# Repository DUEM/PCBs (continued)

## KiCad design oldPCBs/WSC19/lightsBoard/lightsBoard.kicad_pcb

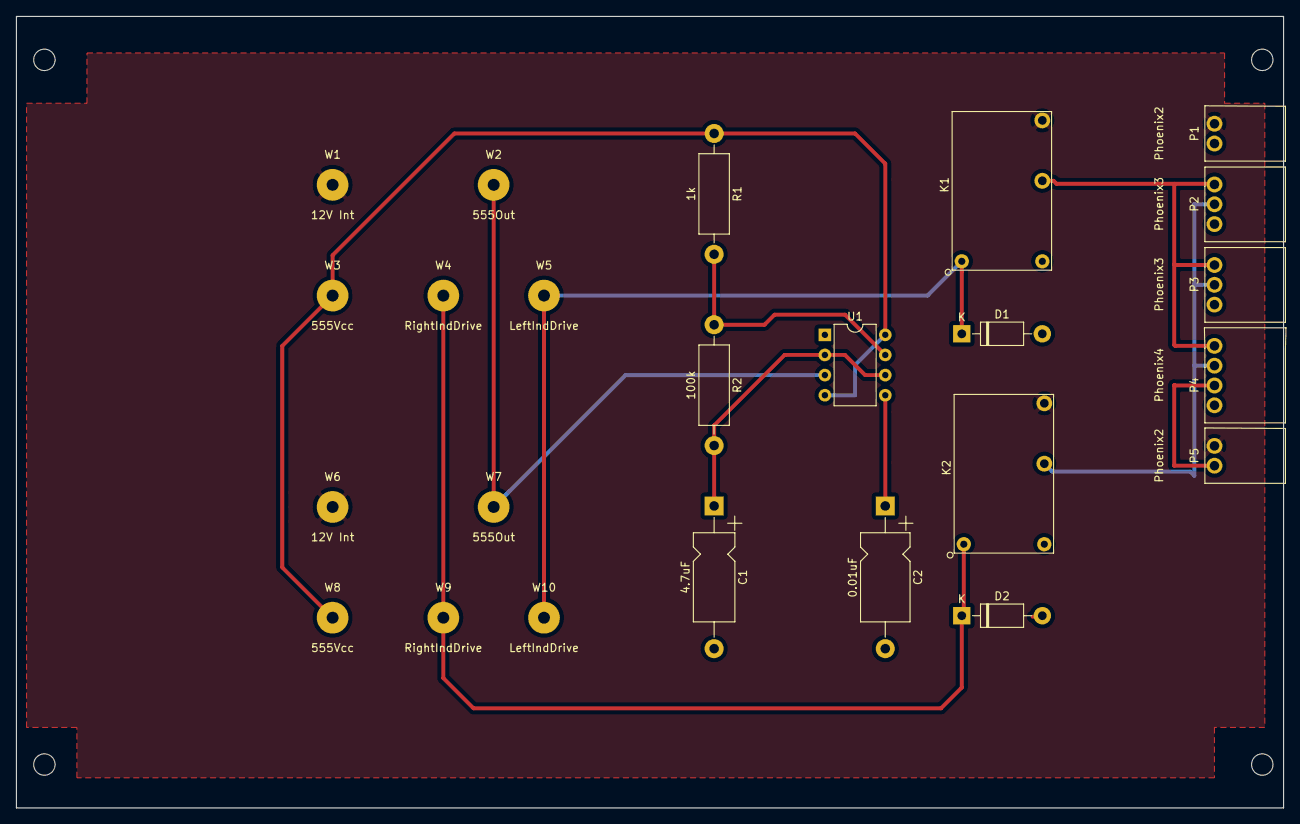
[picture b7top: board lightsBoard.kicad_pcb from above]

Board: 2 copper layers, 159.9 x 99.9 mm, 28 parts (0 on the bottom side), 12 nets.

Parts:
C1: 4.7uF; CP_Axial_L11.0mm_D5.0mm_P18.00mm_Horizontal
C2: 0.01uF; CP_Axial_L11.0mm_D6.0mm_P18.00mm_Horizontal
D1, D2: 1N4001; D_DO-41_SOD81_P10.16mm_Horizontal
K1, K2: DK; DKRelay
MK1, MK2, MK3, MK4: Mounting_Hole_PAD; MountingHole_2.7mm
P1, P5: Phoenix2; PhoenixSmol2
P2, P3: Phoenix3; PhoenixSmol3
P4: Phoenix4; PhoenixSmol4
R1: 1k; R_Axial_DIN0411_L9.9mm_D3.6mm_P15.24mm_Horizontal
R2: 100k; R_Axial_DIN0411_L9.9mm_D3.6mm_P15.24mm_Horizontal
U1: 555Timer; DIP-8_W7.62mm
W1, W6: 12V Int; SolderWirePad_1x01_Drill1.5mm
W2, W7: 555Out; SolderWirePad_1x01_Drill1.5mm
W3, W8: 555Vcc; SolderWirePad_1x01_Drill1.5mm
W4, W9: RightIndDrive; SolderWirePad_1x01_Drill1.5mm
W5, W10: LeftIndDrive; SolderWirePad_1x01_Drill1.5mm

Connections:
+12V: K1.4, K2.4, P1.1, P5.1, W1.1, W6.1
GND: C1.2, C2.2, D1.2, D2.2, K1.1, K2.1, P1.2, P2.3, P3.3, P4.4, U1.1
LeftDrive: D1.1, K1.6, W5.1, W10.1
unnamed: C1.1, R2.2, U1.2, U1.6
unnamed: C2.1, U1.5
unnamed: K1.3, P2.1, P3.1, P4.1
unnamed: K2.3, P2.2, P3.2, P4.2
unnamed: P4.3, P5.2
unnamed: R1.2, R2.1, U1.7
RightDrive: D2.1, K2.6, W4.1, W9.1
Vcc: R1.1, U1.4, U1.8, W3.1, W8.1
Vout: U1.3, W2.1, W7.1

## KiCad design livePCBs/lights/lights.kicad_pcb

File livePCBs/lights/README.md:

# Lights Board
- For iESC 2020
- The `const_current` components are separate daughterboards intended to supply a controllable constant current. These didn't work :( but the design files are on the DUSC drive.

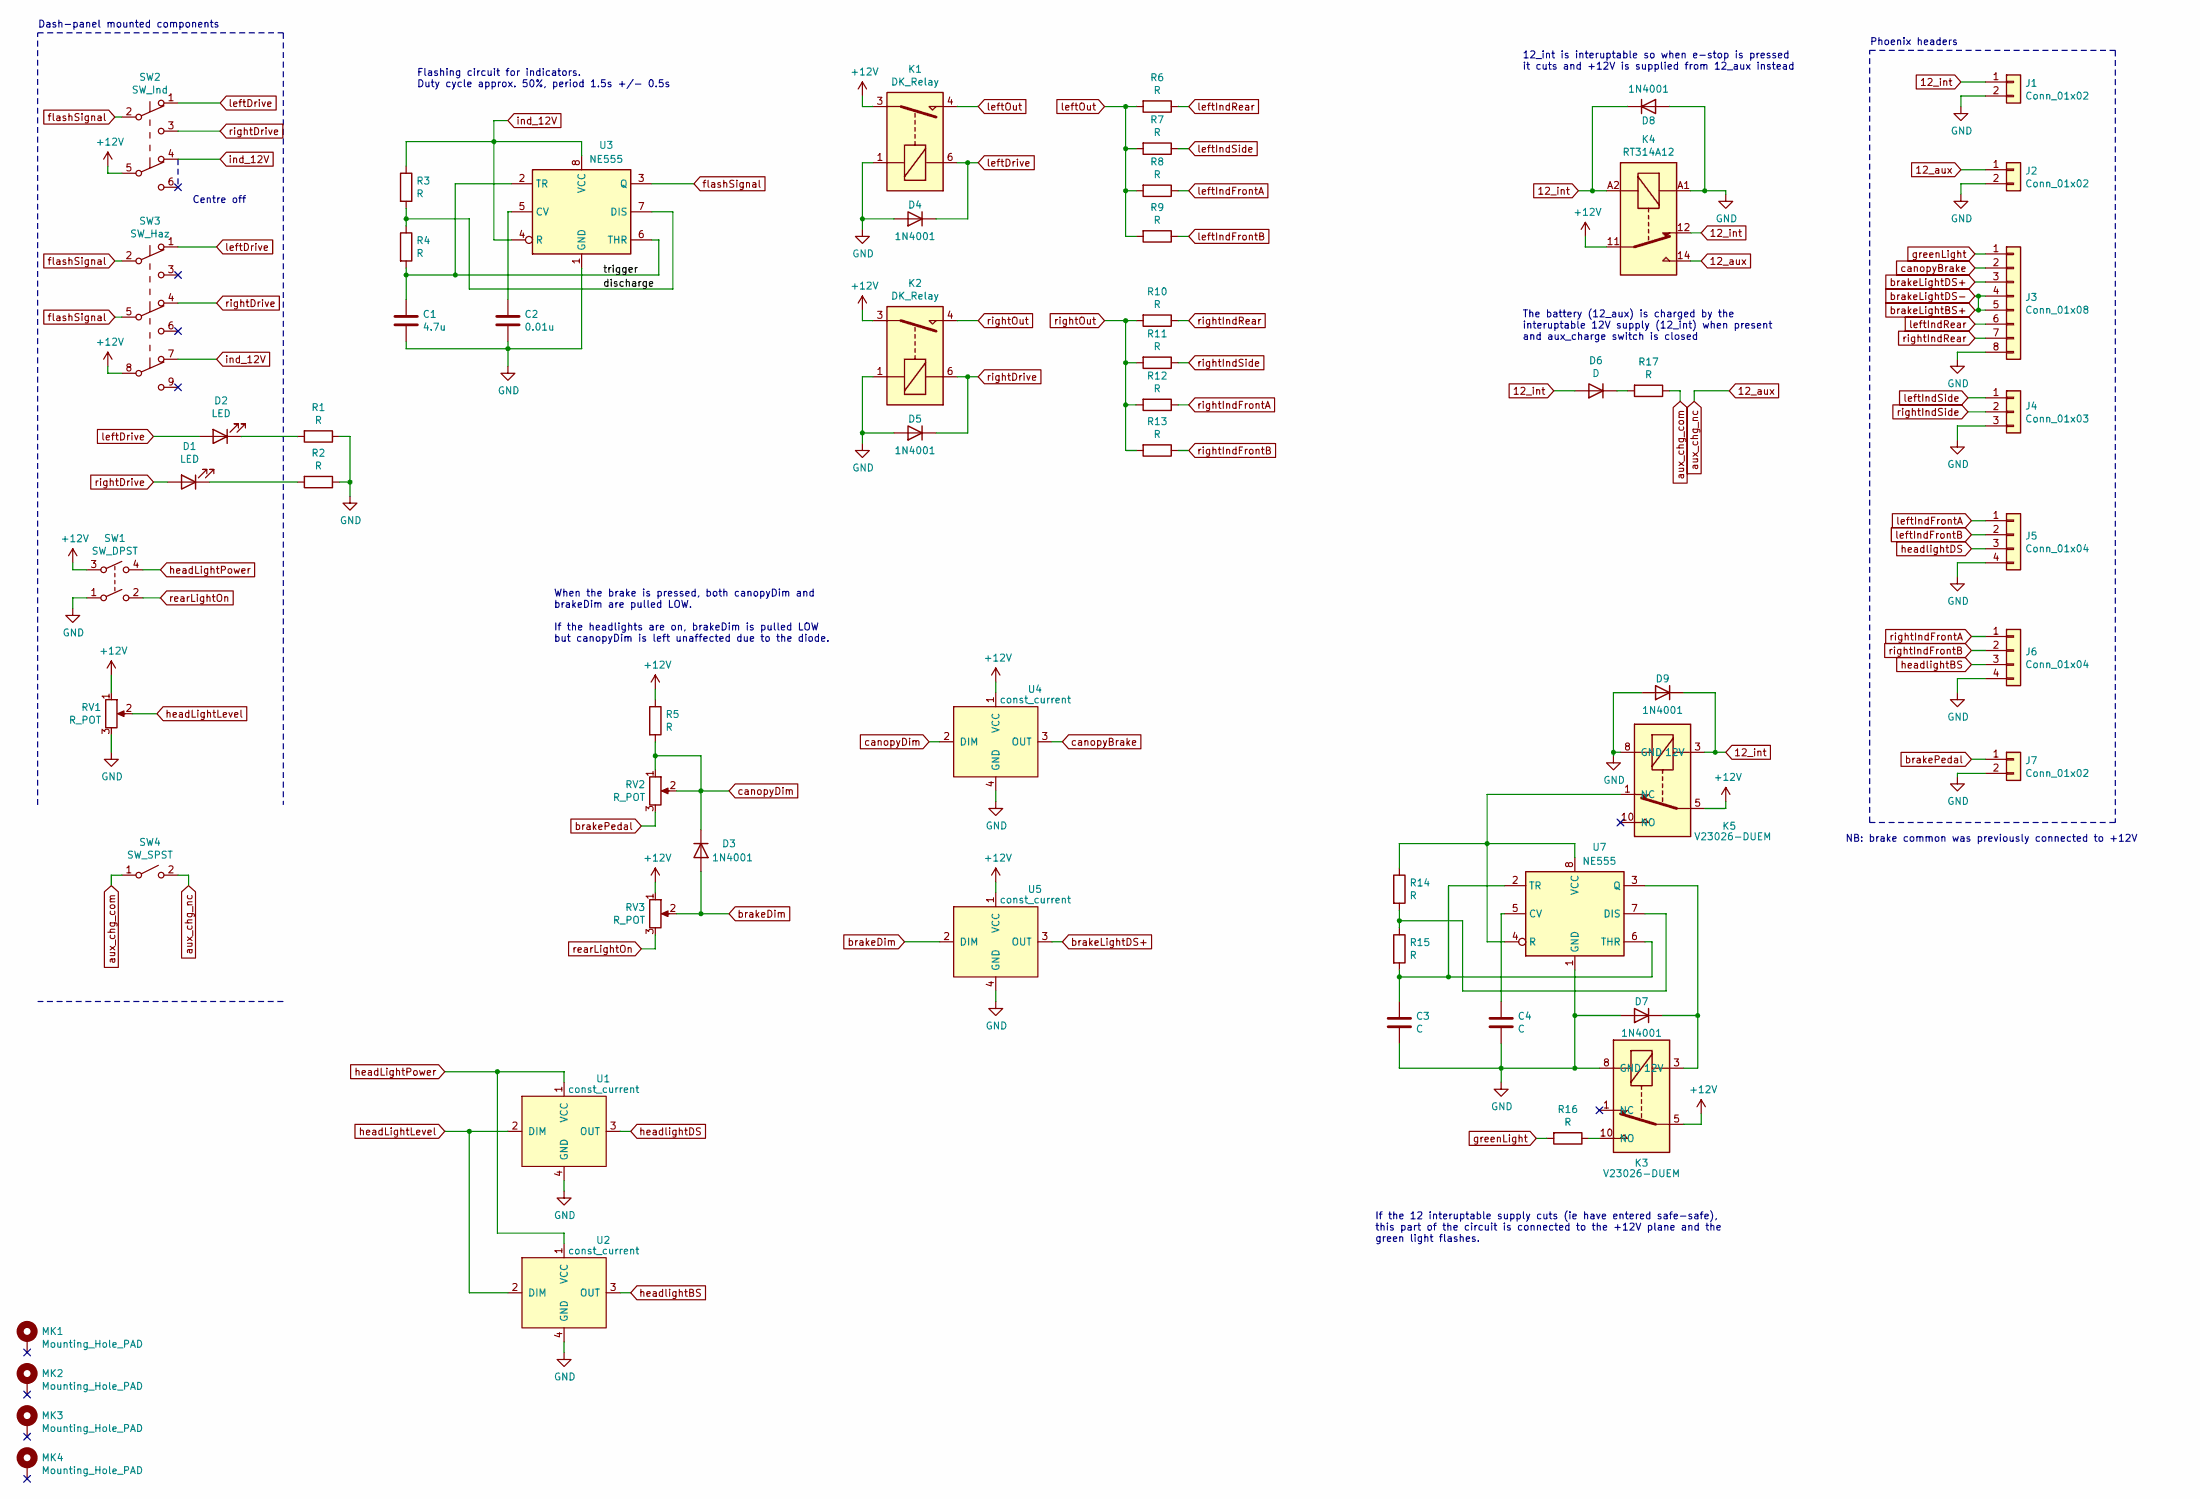
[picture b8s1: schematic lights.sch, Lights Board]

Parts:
C1: 4.7u; CP_Radial_D5.0mm_P2.50mm
C2: 0.01u; C_Disc_D5.0mm_W2.5mm_P2.50mm
C3: C; CP_Radial_D5.0mm_P2.50mm
C4: C; C_Disc_D5.0mm_W2.5mm_P2.50mm
D1, D2: LED; flywire_2
D3, D4, D5, D7, D8, D9: 1N4001; D_DO-41_SOD81_P10.16mm_Horizontal
D6: D; D_DO-41_SOD81_P10.16mm_Horizontal
J1, J2, J7: Conn_01x02; Phoenix_2Way_P2.5mm
J3: Conn_01x08; Phoenix_8Way_P2.5mm
J4: Conn_01x03; Phoenix_3Way_P2.5mm
J5, J6: Conn_01x04; Phoenix_4Way_P2.5mm
K1, K2: DK_Relay
K3, K5: V23026-DUEM; Relay_SPDT_Omron-G5Q-1
K4: RT314A12; Relay_SPDT_Schrack-RT1-16A-FormC_RM5mm
MK1, MK2, MK3, MK4: Mounting_Hole_PAD; MountingHole_2.7mm
R1, R2, R3, R4: R; R_Axial_DIN0207_L6.3mm_D2.5mm_P10.16mm_Horizontal
R5, R14, R15, R16: R; R_Axial_DIN0411_L9.9mm_D3.6mm_P12.70mm_Horizontal
R6, R7, R8, R9, R10, R11, R12, R13, R17: R; R_Axial_DIN0614_L14.3mm_D5.7mm_P25.40mm_Horizontal
RV1: R_POT; flywire_3
RV2, RV3: R_POT; trim_pot_3296W
SW1: SW_DPST; flywire_4
SW2: SW_Ind; flywire_5
SW3: SW_Haz; flywire_6_special_haz
SW4: SW_SPST; flywire_2
U1, U2, U4, U5: const_current; const_current_board_v1
U3, U7: NE555; DIP-8_W7.62mm_Socket

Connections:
12_aux: J2.1, K4.14, SW4.2 (B)
12_int: D6.2 (A), D8.1 (K), D9.1 (K), J1.1, K4.12, K4.A2, K5.3 (12V)
+12V: K1.3, K2.3, K3.5, K4.11, K5.5, R5.1, RV1.1, RV3.1, SW1.3, SW2.5 (B), SW3.8 (B), U4.1 (VCC), U5.1 (VCC)
/discharge: R3.2, R4.1, U3.7 (DIS)
/trigger: C1.1, R4.2, U3.2 (TR), U3.6 (THR)
GND: C1.2, C2.2, C3.2, C4.2, D4.2 (A), D5.2 (A), D7.2 (A), D8.2 (A), D9.2 (A), J1.2, J2.2, J3.8, J4.3, J5.4, J6.4, J7.2, K1.1, K2.1, K3.8 (GND), K4.A1, K5.8 (GND), R1.1, R2.1, RV1.3, SW1.1, U1.4 (GND), U2.4 (GND), U3.1 (GND), U4.4 (GND), U5.4 (GND), U7.1 (GND)
unnamed: C2.1, U3.5 (CV)
unnamed: C3.1, R15.2, U7.2 (TR), U7.6 (THR)
unnamed: C4.1, U7.5 (CV)
unnamed: D1.1 (K), R2.2
unnamed: D2.1 (K), R1.2
unnamed: D6.1 (K), R17.2
unnamed: D7.1 (K), K3.3 (12V), U7.3 (Q)
unnamed: K3.10 (NO), R16.1
unnamed: K5.1 (NC), R14.1, U7.4 (R), U7.8 (VCC)
unnamed: R14.2, R15.1, U7.7 (DIS)
aux_chg_com: R17.1, SW4.1 (A)
brakeDim: D3.2 (A), RV3.2, U5.2 (DIM)
brakeLightBS+: J3.4, J3.5
brakeLightDS+: J3.3, U5.3 (OUT)
brakePedal: J7.1, RV2.3
canopyBrake: J3.2, U4.3 (OUT)
canopyDim: D3.1 (K), R5.2, RV2.1, RV2.2, U4.2 (DIM)
flashSignal: SW2.2 (B), SW3.2 (B), SW3.5 (B), U3.3 (Q)
greenLight: J3.1, R16.2
headLightLevel: RV1.2, U1.2 (DIM), U2.2 (DIM)
headLightPower: SW1.4, U1.1 (VCC), U2.1 (VCC)
headlightBS: J6.3, U2.3 (OUT)
headlightDS: J5.3, U1.3 (OUT)
ind_12V: R3.1, SW2.4 (A), SW3.7 (A), U3.4 (R), U3.8 (VCC)
leftDrive: D2.2 (A), D4.1 (K), K1.6, SW2.1 (A), SW3.1 (A)
leftIndFrontA: J5.1, R8.1
leftIndFrontB: J5.2, R9.1
leftIndRear: J3.6, R6.1
leftIndSide: J4.1, R7.1
leftOut: K1.4, R6.2, R7.2, R8.2, R9.2
rearLightOn: RV3.3, SW1.2
rightDrive: D1.2 (A), D5.1 (K), K2.6, SW2.3 (C), SW3.4 (A)
rightIndFrontA: J6.1, R12.1
rightIndFrontB: J6.2, R13.1
rightIndRear: J3.7, R10.1
rightIndSide: J4.2, R11.1
rightOut: K2.4, R10.2, R11.2, R12.2, R13.2

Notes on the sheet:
Dash-panel mounted components
Phoenix headers
12_int is interuptable so when e-stop is pressed it cuts and +12V is supplied from 12_aux instead
The battery (12_aux) is charged by the interuptable 12V supply (12_int) when present and aux_charge switch is closed
Centre off
NB: brake common was previously connected to +12V
When the brake is pressed, both canopyDim and brakeDim are pulled LOW. If the headlights are on, brakeDim is pulled LOW but canopyDim is left unaffected due to the diode.
If the 12 interuptable supply cuts (ie have entered safe-safe), this part of the circuit is connected to the +12V plane and the green light flashes.
Flashing circuit for indicators. Duty cycle approx. 50%, period 1.5s +/- 0.5s

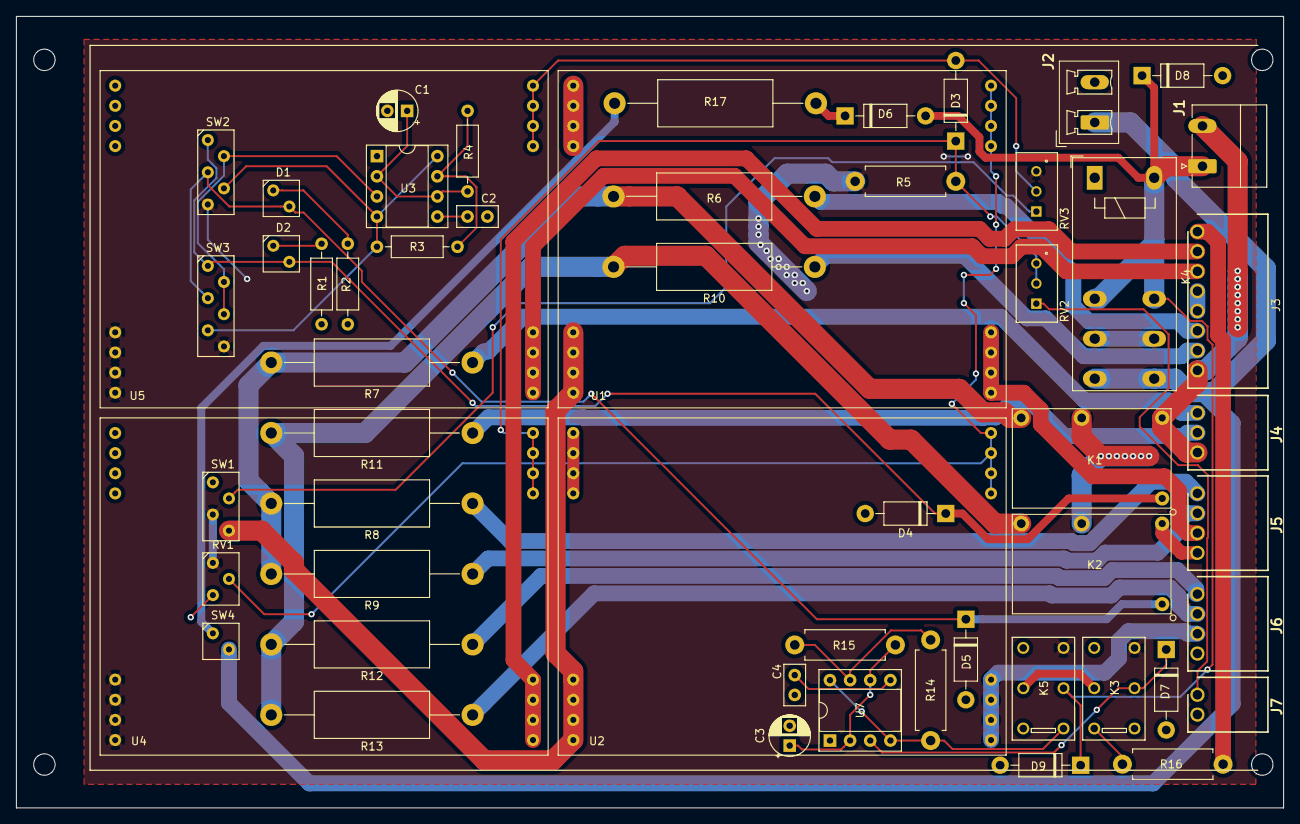
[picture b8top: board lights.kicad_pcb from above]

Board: 2 copper layers, 159.8 x 99.8 mm, 59 parts (0 on the bottom side), 43 nets.

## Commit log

2020-12-23 Add duem library
2020-12-23 Add READMEs
2021-02-04 Add iESC lights board
2021-02-04 Add driver controls schematic - NO PCB
2021-02-04 Add WSC19 lights
2021-02-04 Add WSC19 Orion Board
2021-02-04 Add WSC19 dash and batt power boards
2021-02-04 Keep git happy...
2021-02-19 Correct 12V and GND planes
2021-08-26 DUEM logos
2021-12-23 Original 2023 Resistor Lights board
    Original lights board idea that used resistors. Constant Current version was to follow. New idea coming instead,
